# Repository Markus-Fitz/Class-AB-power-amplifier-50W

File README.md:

# Class-AB-power-amplifier-50W
 Class AB power amplifier designed for 25W into 8 Ohms and 50W into 4 Ohms.

# Specs
 This Power amplifier consists of a Darlington-pair of TIP41C- and BD139-transistors and TIP42C- and BD140-transistors. This amplifier was designed for the operation with a +-24V power-supply. The voltage-amplification is done with a OpAmp, which therefore has to withstand the maximum supply voltages. A Vbe-multiplier mounted to the same heatsink is responsible for a stable bias current throung the endstage and can be adjusted for different bias current settings.

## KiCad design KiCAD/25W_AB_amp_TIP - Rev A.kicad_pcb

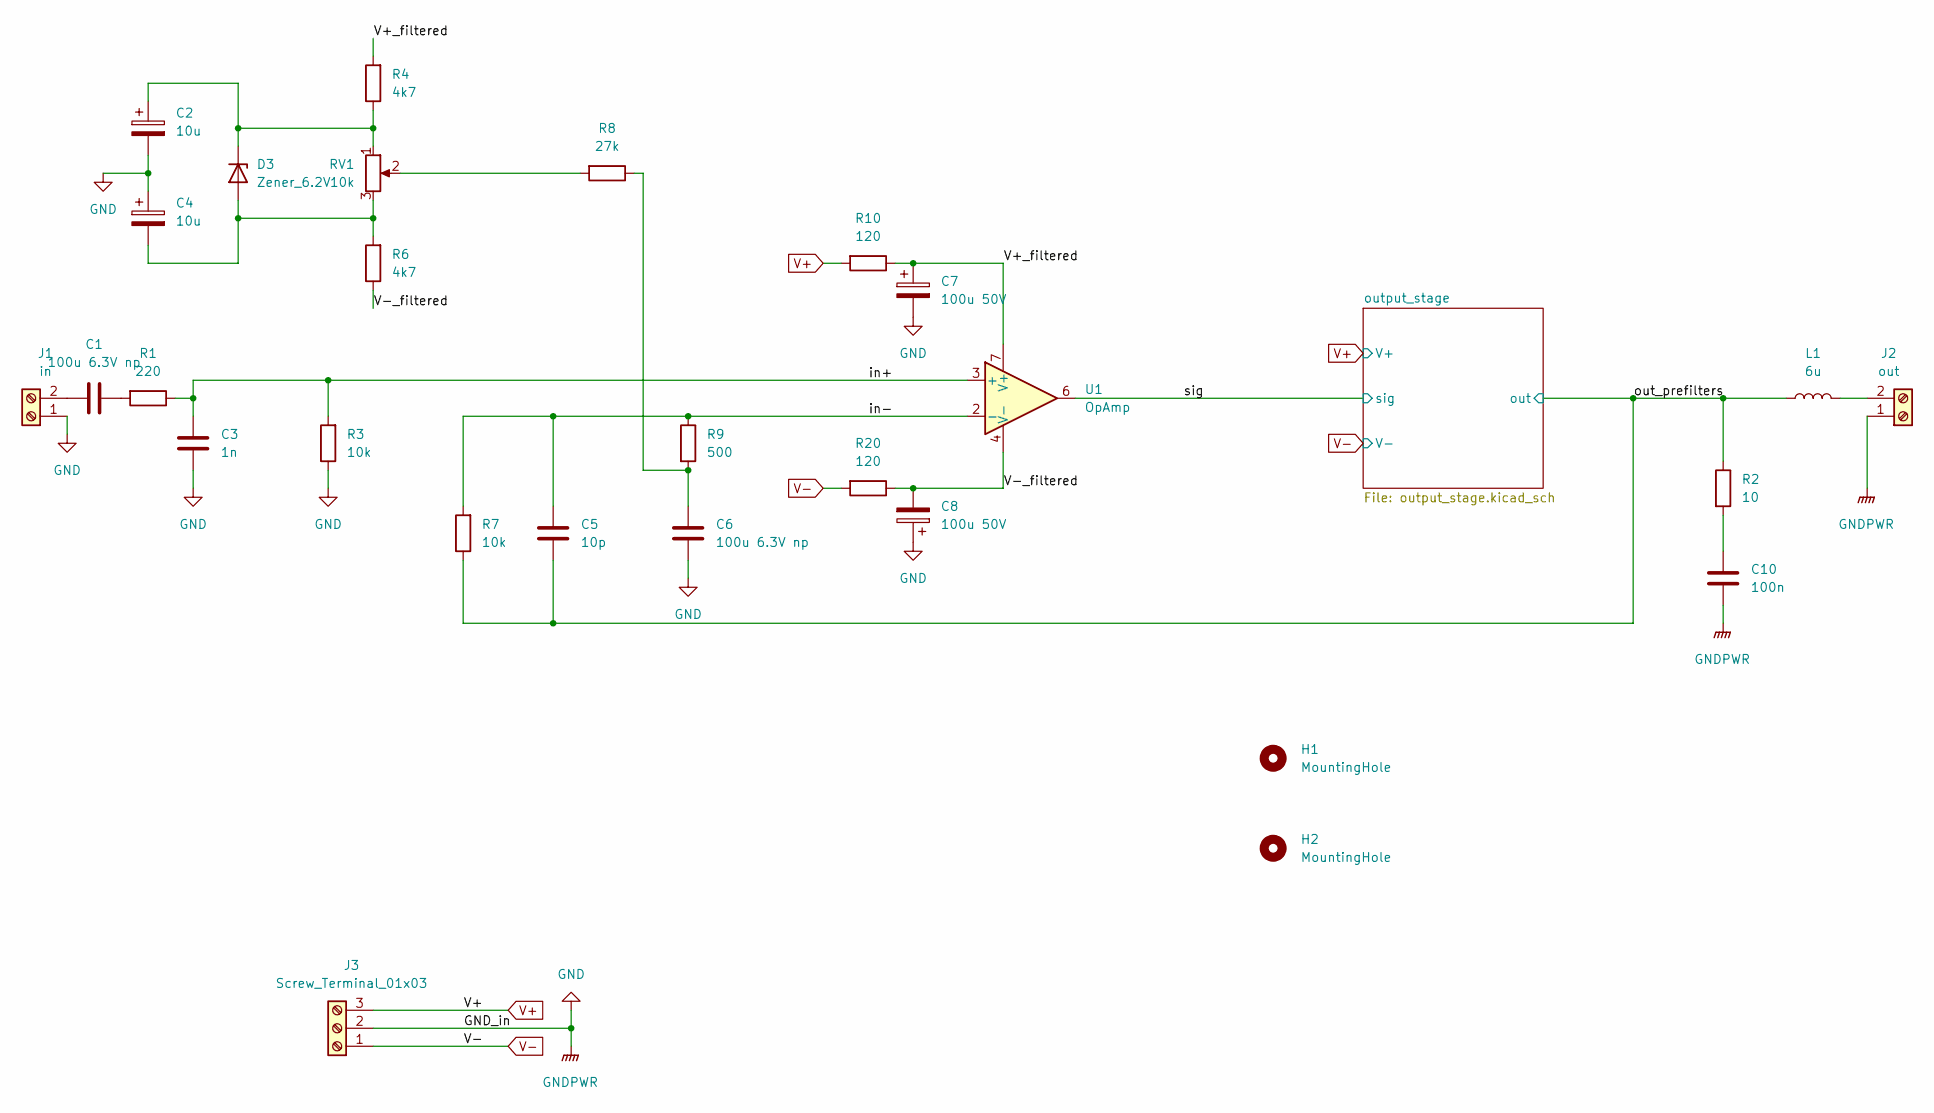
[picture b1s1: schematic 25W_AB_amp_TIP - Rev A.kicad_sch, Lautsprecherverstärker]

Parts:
C1, C6: 100u 6.3V np; C_Radial_D8.0mm_H11.5mm_P3.50mm
C2, C4: 10u; CP_Radial_D5.0mm_P2.00mm
C3: 1n; C_Rect_L7.0mm_W3.5mm_P5.00mm
C5: 10p; C_Disc_D5.1mm_W3.2mm_P5.00mm
C7, C8: 100u 50V; CP_Radial_D8.0mm_P3.50mm
C10: 100n; C_Disc_D5.1mm_W3.2mm_P5.00mm
D3: Zener_6.2V; D_DO-35_SOD27_P7.62mm_Horizontal
H1, H2: MountingHole; MountingHole_3.2mm_M3
J1: in; TerminalBlock_bornier-2_P5.08mm
J2: out; TerminalBlock_bornier-2_P5.08mm
J3: Screw_Terminal_01x03; TerminalBlock_bornier-3_P5.08mm
L1: 6u; L_Radial_D7.5mm_P5.00mm_Fastron_07P
R1: 220; R_Axial_DIN0207_L6.3mm_D2.5mm_P10.16mm_Horizontal
R2: 10; R_Axial_DIN0207_L6.3mm_D2.5mm_P10.16mm_Horizontal
R3, R7: 10k; R_Axial_DIN0207_L6.3mm_D2.5mm_P10.16mm_Horizontal
R4, R6: 4k7; R_Axial_DIN0207_L6.3mm_D2.5mm_P10.16mm_Horizontal
R8: 27k; R_Axial_DIN0207_L6.3mm_D2.5mm_P10.16mm_Horizontal
R9: 500; R_Axial_DIN0207_L6.3mm_D2.5mm_P10.16mm_Horizontal
R10, R20: 120; R_Axial_DIN0207_L6.3mm_D2.5mm_P10.16mm_Horizontal
RV1: 10k; Potentiometer_Bourns_3296W_Vertical
U1: OpAmp; DIP-8_W7.62mm_Socket

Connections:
/V+_filtered: C7.1, R4.2, R10.1, U1.7 (V+)
/V-_filtered: C8.2, R6.1, R20.1, U1.4 (V-)
/in+: C3.1, R1.1, R3.2, U1.3 (+)
/in-: C5.2, R7.2, R9.1, U1.2 (-)
/out_prefilters: C5.1, L1.1, R2.1, R7.1; also elsewhere on the board
/sig: U1.6; also elsewhere on the board
GND: C2.2, C3.2, C4.1, C6.1, C7.2, C8.1, C10.1, J1.1, J2.1, J3.2, R3.1
unnamed: C1.1, J1.2
unnamed: C1.2, R1.2
unnamed: C2.1, D3.1 (K), R4.1, RV1.1
unnamed: C4.2, D3.2 (A), R6.2, RV1.3
unnamed: C6.2, R8.1, R9.2
unnamed: C10.2, R2.2
unnamed: J2.2, L1.2
unnamed: R8.2, RV1.2
V+: J3.3, R10.2; also elsewhere on the board
V-: J3.1, R20.2; also elsewhere on the board

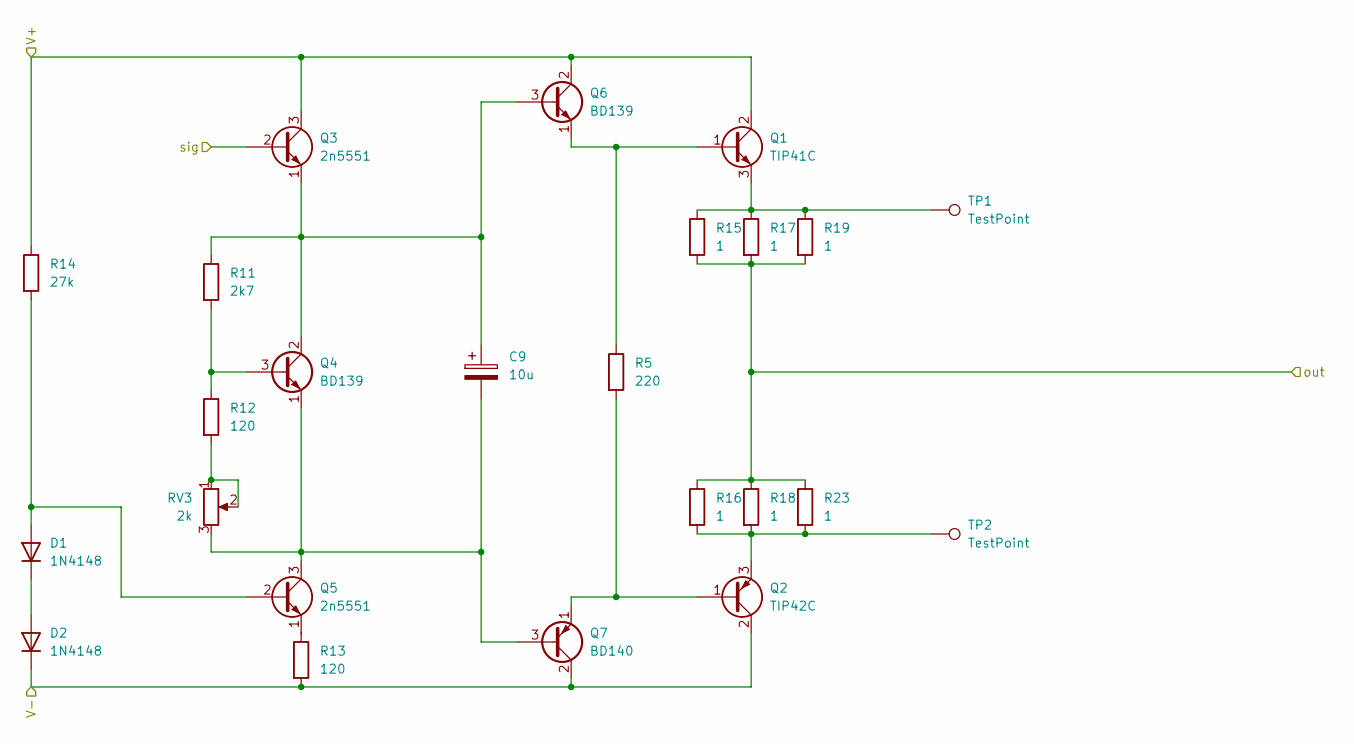
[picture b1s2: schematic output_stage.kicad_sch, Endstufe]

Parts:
C9: 10u; CP_Radial_D5.0mm_P2.00mm
D1, D2: 1N4148; D_DO-35_SOD27_P7.62mm_Horizontal
Q1: TIP41C; TO-220-3_Vertical
Q2: TIP42C; TO-220-3_Vertical
Q3, Q5: 2n5551; TO-92_Inline_Wide
Q4, Q6: BD139; TO-126-3_Vertical
Q7: BD140; TO-126-3_Vertical
R5: 220; R_Axial_DIN0207_L6.3mm_D2.5mm_P10.16mm_Horizontal
R11: 2k7; R_Axial_DIN0207_L6.3mm_D2.5mm_P10.16mm_Horizontal
R12, R13: 120; R_Axial_DIN0207_L6.3mm_D2.5mm_P10.16mm_Horizontal
R14: 27k; R_Axial_DIN0207_L6.3mm_D2.5mm_P10.16mm_Horizontal
R15, R16, R17, R18, R19, R23: 1; R_Axial_DIN0207_L6.3mm_D2.5mm_P10.16mm_Horizontal
RV3: 2k; Potentiometer_Bourns_3296W_Vertical
TP1, TP2: TestPoint; TestPoint_Pad_D2.0mm

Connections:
/out_prefilters: R15.2, R16.1, R17.2, R18.1, R19.2, R23.1; also elsewhere on the board
/sig: Q3.2 (B); also elsewhere on the board
unnamed: C9.1, Q3.1 (E), Q4.2 (C), Q6.3 (B), R11.1
unnamed: C9.2, Q4.1 (E), Q5.3 (C), Q7.3 (B), RV3.3
unnamed: D1.1 (K), D2.2 (A)
unnamed: D1.2 (A), Q5.2 (B), R14.2
unnamed: Q1.1 (B), Q6.1 (E), R5.1
unnamed: Q1.3 (E), R15.1, R17.1, R19.1, TP1.1
unnamed: Q2.1 (B), Q7.1 (E), R5.2
unnamed: Q2.3 (E), R16.2, R18.2, R23.2, TP2.1
unnamed: Q4.3 (B), R11.2, R12.1
unnamed: Q5.1 (E), R13.1
unnamed: R12.2, RV3.1, RV3.2
V+: Q1.2 (C), Q3.3 (C), Q6.2 (C), R14.1; also elsewhere on the board
V-: D2.1 (K), Q2.2 (C), Q7.2 (C), R13.2; also elsewhere on the board

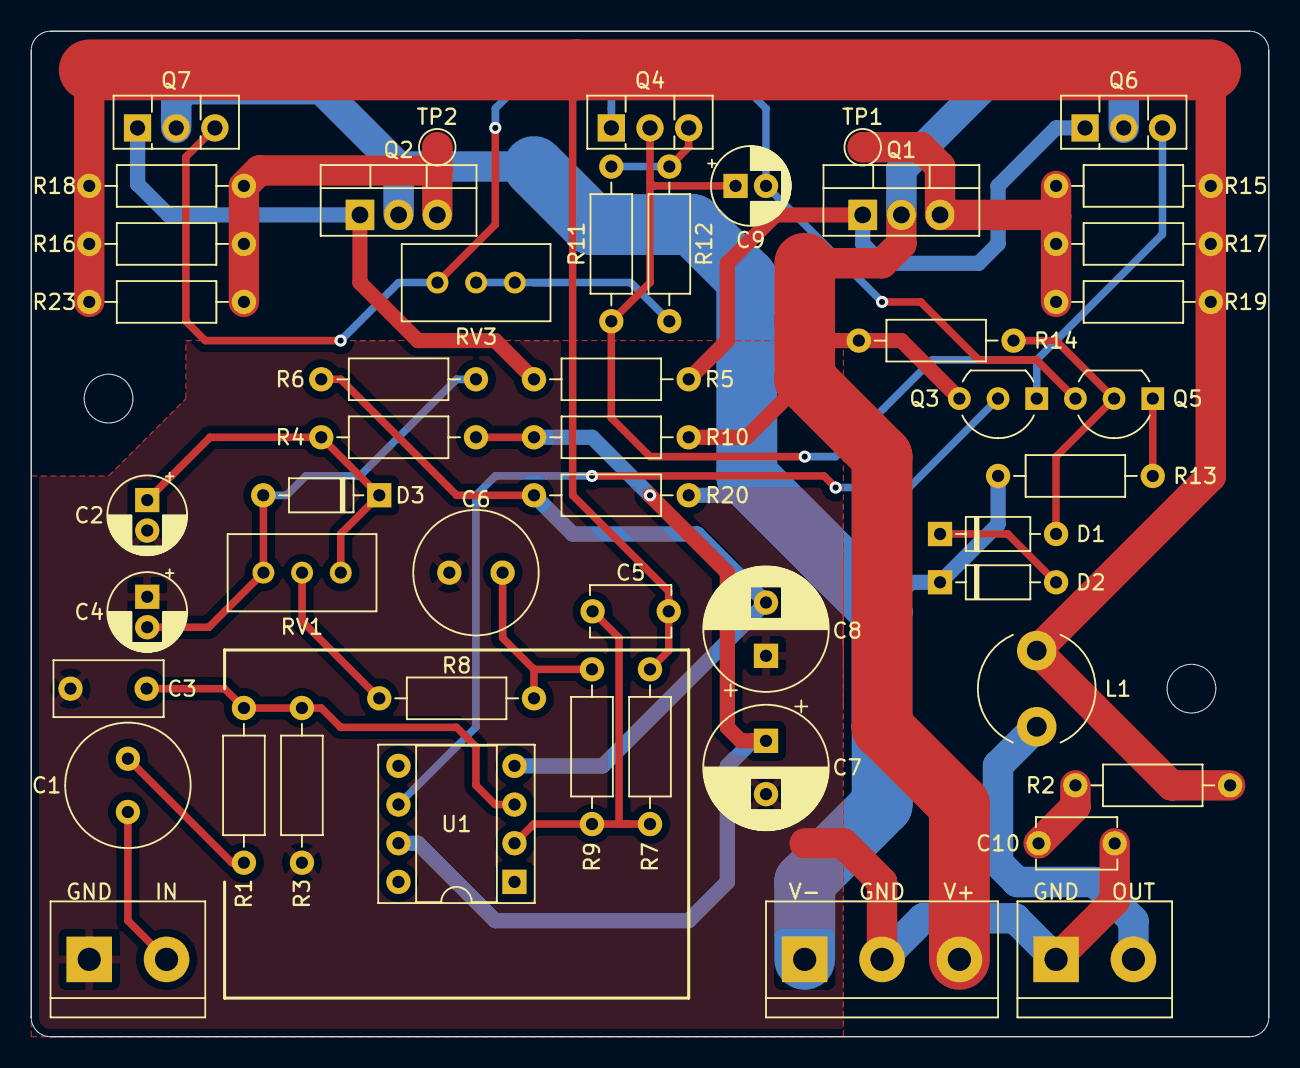
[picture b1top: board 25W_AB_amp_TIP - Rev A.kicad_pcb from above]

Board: 2 copper layers, 81.3 x 66.0 mm, 52 parts (0 on the bottom side), 28 nets.

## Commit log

2024-04-07 Initial commit
    Initial Commit.
2024-04-07 Create LICENSE
    Addition of GNU-license
